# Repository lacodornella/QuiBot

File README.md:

# QuiBot

QuiBot is a robot to experiment basic sequential programming for children. No computer is needed as it can be programmed by using painted wooden blocks, where each color represents a different action. The robot has a backpack that can contain up to 12 blocks that execute as soon as they're consumed.

## Project folders

The project uses the following folders:
 - [3D Design](./3D_design/): 3D assembly process, BOM and printing files
 - [ESP-32 Arduino program](./QuiBot/): C++ Arduino program
 - [Kicad PCB project](./PCB_QuiBot/): Kicad PCB project
 - [Images](./Images/): Used to store some project images

## Development

This robot has been conceived and developed by Aleix Badia and [Pau Lafoz](https://www.github.com/pau-lafoz) from La Codornella under the UPC project "Qui-Bot H2O", led by Marta Tarrés and Toni Dorado, and funded by FECYT.

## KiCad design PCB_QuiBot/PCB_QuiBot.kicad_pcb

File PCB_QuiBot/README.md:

# QuiBot Kicad Project

## 3D View

## Layout

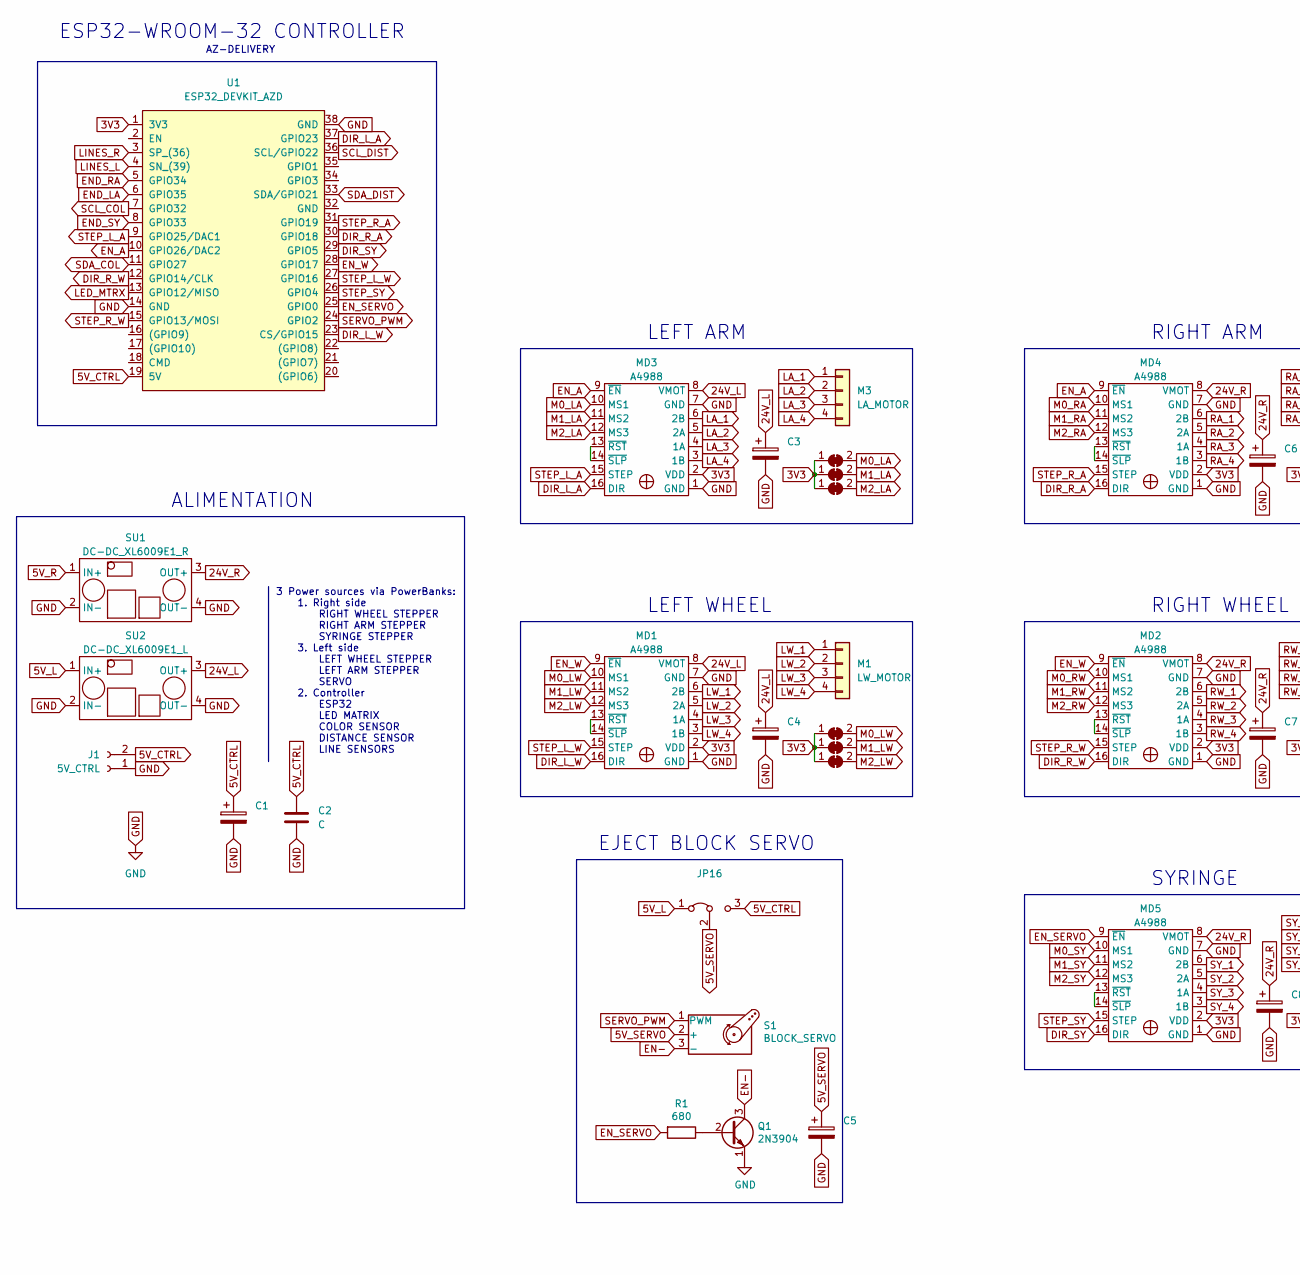
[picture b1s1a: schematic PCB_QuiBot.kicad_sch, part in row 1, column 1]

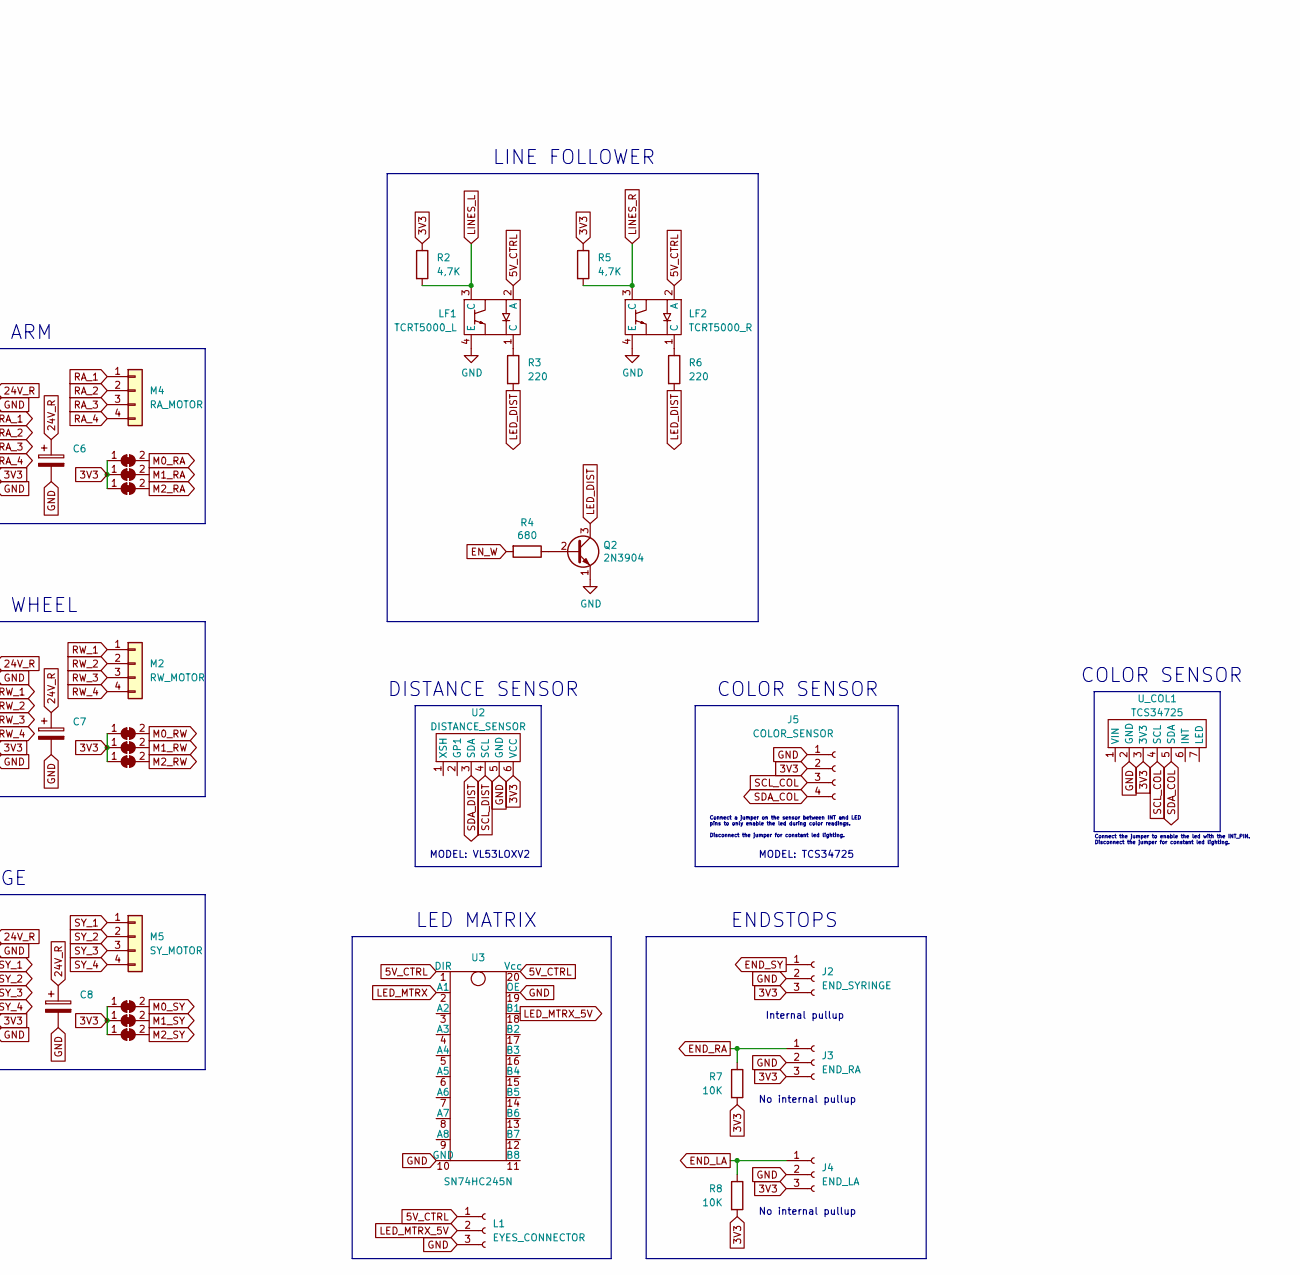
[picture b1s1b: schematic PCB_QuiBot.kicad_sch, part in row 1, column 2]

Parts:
C1: (no value)
C2: C; C_Disc_D4.3mm_W1.9mm_P5.00mm
C3, C4, C5, C6, C7, C8: C_Polarized; CP_Flat_position
J1: 5V_CTRL; PCB_cable_soldering
J2: END_SYRINGE; PinHeader_1x03_P2.54mm_Vertical
J3: END_RA; PinHeader_1x03_P2.54mm_Vertical
J4: END_LA; PinHeader_1x03_P2.54mm_Vertical
J5: COLOR_SENSOR; PinHeader_1x04_P2.54mm_Vertical
JP1, JP2, JP3, JP4, JP5, JP6, JP7, JP8, JP9, JP10, JP11, JP12, JP13, JP14, JP15: SolderJumper_2_Bridged; SolderJumper-2_P1.3mm_Bridged_RoundedPad1.0x1.5mm
JP16: (no value)
L1: EYES_CONNECTOR; PinHeader_1x03_P2.54mm_Vertical
LF1: TCRT5000_L; TCRT5000_Line_follower
LF2: TCRT5000_R; TCRT5000_Line_follower
M1: LW_MOTOR; PinHeader_1x04_P2.54mm_Vertical
M2: RW_MOTOR; PinHeader_1x04_P2.54mm_Vertical
M3: LA_MOTOR; PinHeader_1x04_P2.54mm_Vertical
M4: RA_MOTOR; PinHeader_1x04_P2.54mm_Vertical
M5: SY_MOTOR; PinHeader_1x04_P2.54mm_Vertical
MD1, MD2, MD3, MD4, MD5: A4988; A4988_stepper_driver
Q1, Q2: 2N3904; TO-92_Inline_Wide
R1, R4: 680; R_Axial_DIN0207_L6.3mm_D2.5mm_P10.16mm_Horizontal
R2, R5: 4,7K; R_Axial_DIN0207_L6.3mm_D2.5mm_P10.16mm_Horizontal
R3, R6: 220; R_Axial_DIN0207_L6.3mm_D2.5mm_P10.16mm_Horizontal
R7, R8: 10K; R_Axial_DIN0207_L6.3mm_D2.5mm_P10.16mm_Horizontal
S1: BLOCK_SERVO; PinHeader_1x03_P2.54mm_Vertical
SU1: DC-DC_XL6009E1_R
SU2: DC-DC_XL6009E1_L
U1: ESP32_DEVKIT_AZD; ESP32_DevKit_AZD
U2: DISTANCE_SENSOR; PinHeader_1x06_P2.54mm_Vertical
U3: SN74HC245N
U_COL1: TCS34725

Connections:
3V3: J2.3, J3.3, J4.3, J5.2, JP1.1 (A), JP2.1 (A), JP3.1 (A), JP4.1 (A), JP5.1 (A), JP6.1 (A), JP7.1 (A), JP8.1 (A), JP9.1 (A), JP10.1 (A), JP11.1 (A), JP12.1 (A), JP13.1 (A), JP14.1 (A), JP15.1 (A), MD1.2 (VDD), MD2.2 (VDD), MD3.2 (VDD), MD4.2 (VDD), MD5.2 (VDD), R2.1, R5.1, R7.2, R8.2, U1.1 (3V3), U2.6 (VCC), U_COL1.3 (3V3)
5V_CTRL: C1.1, C2.1, J1.2, JP16.3 (B), L1.1, LF1.2 (A), LF2.2 (A), U1.19 (5V), U3.1 (DIR), U3.20 (Vcc)
5V_L: JP16.1 (A), SU2.1 (IN+)
5V_R: SU1.1 (IN+)
5V_SERVO: C5.1, JP16.2 (C), S1.2 (+)
24V_L: C3.1, C4.1, MD1.8 (VMOT), MD3.8 (VMOT), SU2.3 (OUT+)
24V_R: C6.1, C7.1, C8.1, MD2.8 (VMOT), MD4.8 (VMOT), MD5.8 (VMOT), SU1.3 (OUT+)
DIR_L_A: MD3.16 (DIR), U1.37 (GPIO23)
DIR_L_W: MD1.16 (DIR), U1.23 (CS/GPIO15)
DIR_R_A: MD4.16 (DIR), U1.30 (GPIO18)
DIR_R_W: MD2.16 (DIR), U1.12 (GPIO14/CLK)
DIR_SY: MD5.16 (DIR), U1.29 (GPIO5)
EN-: Q1.3 (C), S1.3 (-)
END_LA: J4.1, R8.1, U1.6 (GPIO35)
END_RA: J3.1, R7.1, U1.5 (GPIO34)
END_SY: J2.1, U1.8 (GPIO33)
EN_A: MD3.9 (~EN), MD4.9 (~EN), U1.10 (GPIO26/DAC2)
EN_SERVO: MD5.9 (~EN), R1.2, U1.25 (GPIO0)
EN_W: MD1.9 (~EN), MD2.9 (~EN), R4.2, U1.28 (GPIO17)
GND: C1.2, C2.2, C3.2, C4.2, C5.2, C6.2, C7.2, C8.2, J1.1, J2.2, J3.2, J4.2, J5.1, L1.3, LF1.4 (E), LF2.4 (E), MD1.1 (GND), MD1.7 (GND), MD2.1 (GND), MD2.7 (GND), MD3.1 (GND), MD3.7 (GND), MD4.1 (GND), MD4.7 (GND), MD5.1 (GND), MD5.7 (GND), Q1.1 (E), Q2.1 (E), SU1.2 (IN-), SU1.4 (OUT-), SU2.2 (IN-), SU2.4 (OUT-), U1.14 (GND), U1.38 (GND), U2.5 (GND), U3.10 (GND), U3.19 (OE), U_COL1.2 (GND)
LA_1: M3.1, MD3.6 (2B)
LA_2: M3.2, MD3.5 (2A)
LA_3: M3.3, MD3.4 (1A)
LA_4: M3.4, MD3.3 (1B)
LED_DIST: Q2.3 (C), R3.2, R6.2
LED_MTRX: U1.13 (GPIO12/MISO), U3.2 (A1)
LED_MTRX_5V: L1.2, U3.18 (B1)
LINES_L: LF1.3 (C), R2.2, U1.4 (SN_(39))
LINES_R: LF2.3 (C), R5.2, U1.3 (SP_(36))
LW_1: M1.1, MD1.6 (2B)
LW_2: M1.2, MD1.5 (2A)
LW_3: M1.3, MD1.4 (1A)
LW_4: M1.4, MD1.3 (1B)
M0_LA: JP1.2 (B), MD3.10 (MS1)
M0_LW: JP4.2 (B), MD1.10 (MS1)
M0_RA: JP7.2 (B), MD4.10 (MS1)
M0_RW: JP10.2 (B), MD2.10 (MS1)
M0_SY: JP13.2 (B), MD5.10 (MS1)
M1_LA: JP2.2 (B), MD3.11 (MS2)
M1_LW: JP5.2 (B), MD1.11 (MS2)
M1_RA: JP8.2 (B), MD4.11 (MS2)
M1_RW: JP11.2 (B), MD2.11 (MS2)
M1_SY: JP14.2 (B), MD5.11 (MS2)
M2_LA: JP3.2 (B), MD3.12 (MS3)
M2_LW: JP6.2 (B), MD1.12 (MS3)
M2_RA: JP9.2 (B), MD4.12 (MS3)
M2_RW: JP12.2 (B), MD2.12 (MS3)
M2_SY: JP15.2 (B), MD5.12 (MS3)
unnamed: LF1.1 (C), R3.1
unnamed: LF2.1 (C), R6.1
unnamed: MD1.13 (~RST), MD1.14 (~SLP)
unnamed: MD2.13 (~RST), MD2.14 (~SLP)
unnamed: MD3.13 (~RST), MD3.14 (~SLP)
unnamed: MD4.13 (~RST), MD4.14 (~SLP)
unnamed: MD5.13 (~RST), MD5.14 (~SLP)
unnamed: Q1.2 (B), R1.1
unnamed: Q2.2 (B), R4.1
RA_1: M4.1, MD4.6 (2B)
RA_2: M4.2, MD4.5 (2A)
RA_3: M4.3, MD4.4 (1A)
RA_4: M4.4, MD4.3 (1B)
RW_1: M2.1, MD2.6 (2B)
RW_2: M2.2, MD2.5 (2A)
RW_3: M2.3, MD2.4 (1A)
RW_4: M2.4, MD2.3 (1B)
SCL_COL: J5.3, U1.7 (GPIO32), U_COL1.4 (SCL)
SCL_DIST: U1.36 (SCL/GPIO22), U2.4 (SCL)
SDA_COL: J5.4, U1.11 (GPIO27), U_COL1.5 (SDA)
SDA_DIST: U1.33 (SDA/GPIO21), U2.3 (SDA)
SERVO_PWM: S1.1 (PWM), U1.24 (GPIO2)
STEP_L_A: MD3.15 (STEP), U1.9 (GPIO25/DAC1)
STEP_L_W: MD1.15 (STEP), U1.27 (GPIO16)
STEP_R_A: MD4.15 (STEP), U1.31 (GPIO19)
STEP_R_W: MD2.15 (STEP), U1.15 (GPIO13/MOSI)
STEP_SY: MD5.15 (STEP), U1.26 (GPIO4)
SY_1: M5.1, MD5.6 (2B)
SY_2: M5.2, MD5.5 (2A)
SY_3: M5.3, MD5.4 (1A)
SY_4: M5.4, MD5.3 (1B)

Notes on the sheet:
No internal pullup
ALIMENTATION
MODEL: VL53LOXV2
RIGHT WHEEL
MODEL: TCS34725
COLOR SENSOR
EJECT BLOCK SERVO
ENDSTOPS
LEFT ARM
ESP32-WROOM-32 CONTROLLER
AZ-DELIVERY
SYRINGE
LINE FOLLOWER
Connect a jumper on the sensor between INT and LED pins to only enable the led during color readings. Disconnect the jumper for constant led lighting.
LEFT WHEEL
DISTANCE SENSOR
LED MATRIX
3 Power sources via PowerBanks: 1. Right side RIGHT WHEEL STEPPER RIGHT ARM STEPPER SYRINGE STEPPER 3. Left side LEFT WHEEL STEPPER LEFT ARM STEPPER SERVO 2. Controller ESP32 LED MATRIX COLOR SENSOR DISTANCE SENSOR LINE SENSORS
Internal pullup
Connect the jumper to enable the led with the INT_PIN. Disconnect the jumper for constant led lighting.
RIGHT ARM

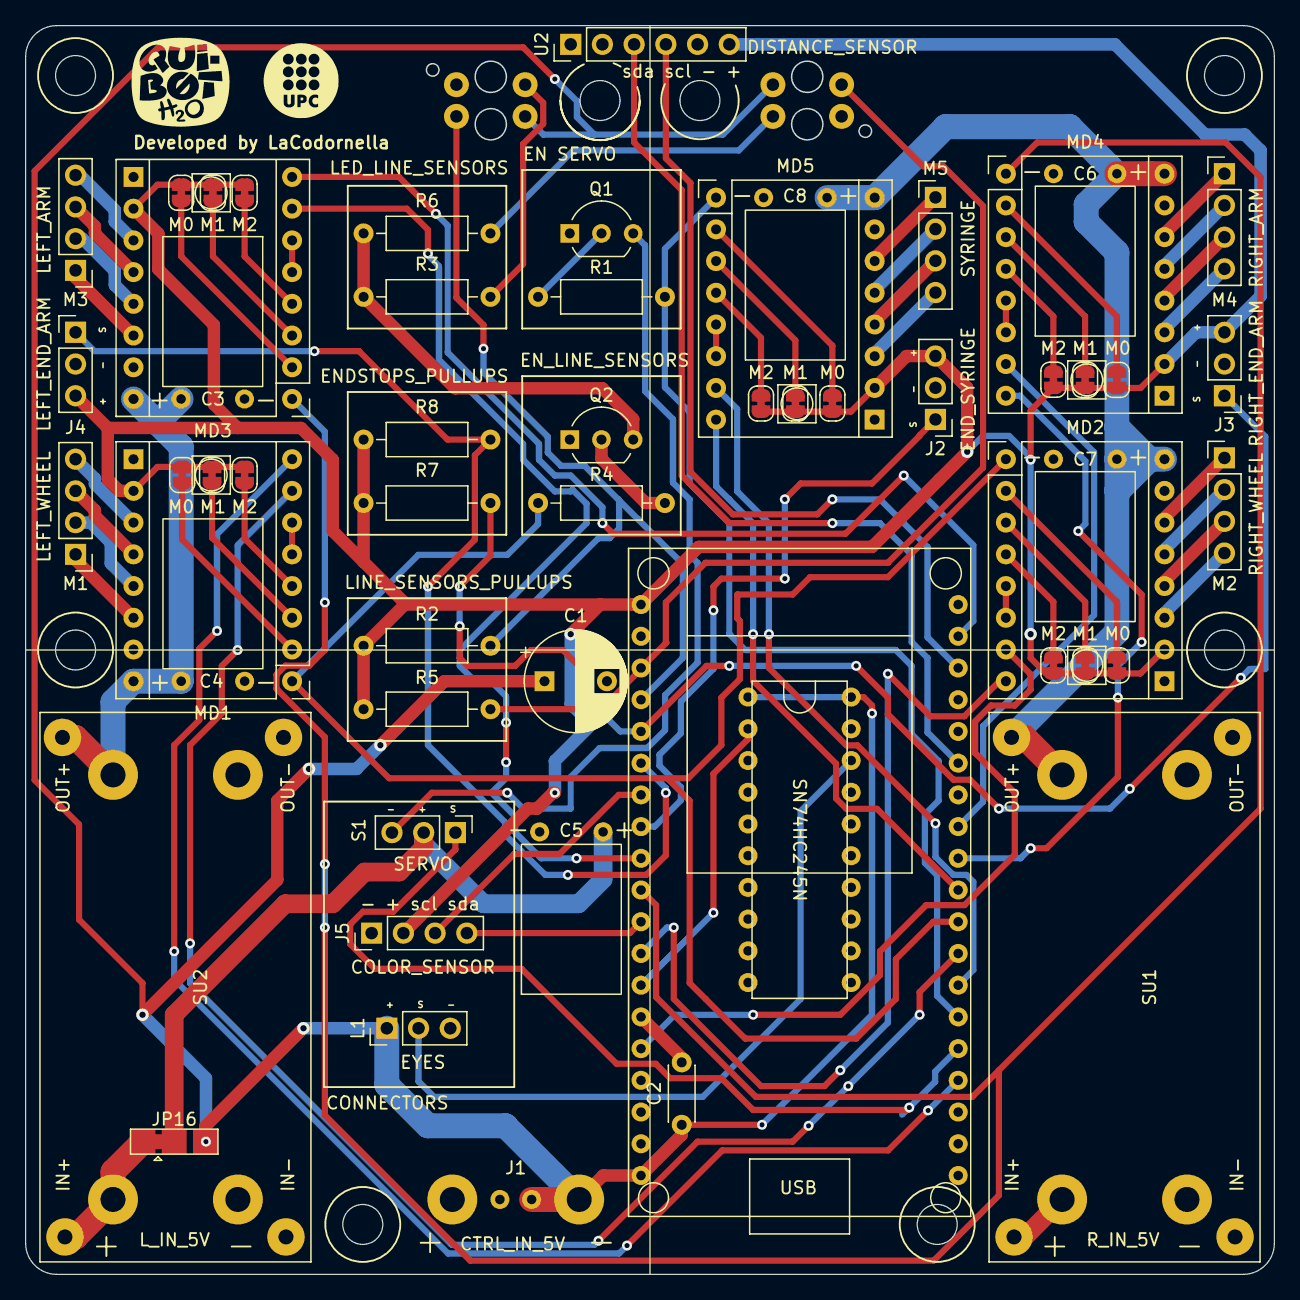
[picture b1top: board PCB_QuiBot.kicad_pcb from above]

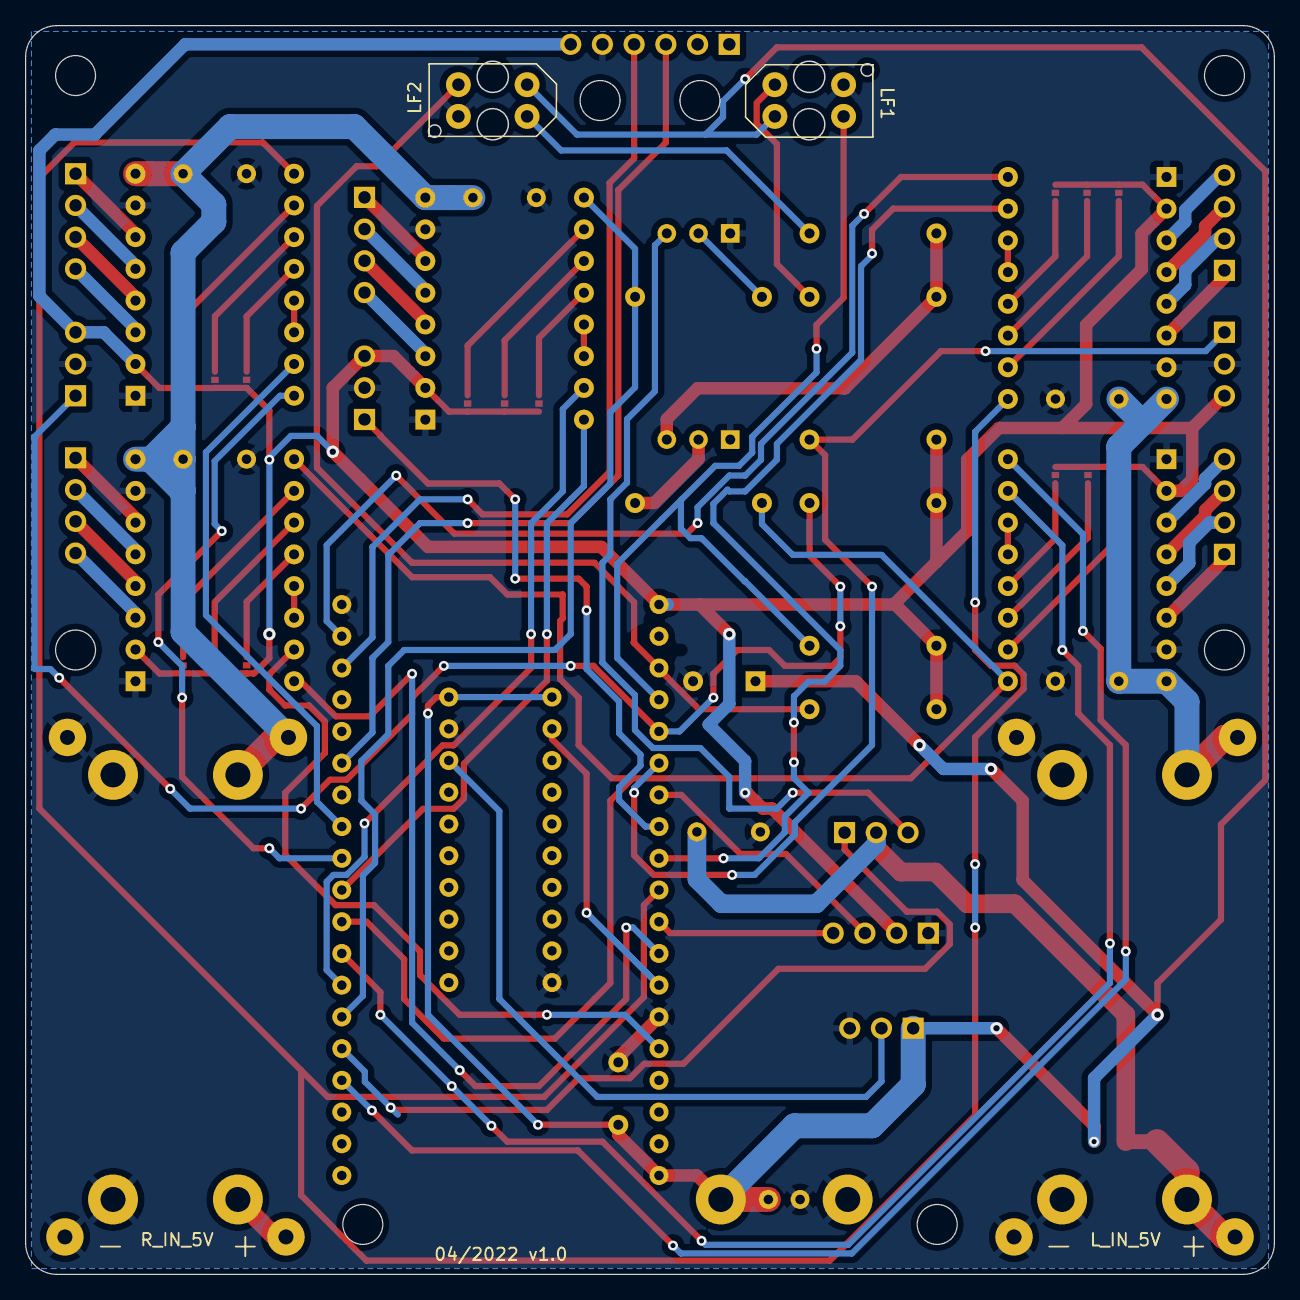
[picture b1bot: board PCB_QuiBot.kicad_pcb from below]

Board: 2 copper layers, 100.0 x 100.0 mm, 58 parts (2 on the bottom side), 78 nets.

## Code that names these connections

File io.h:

#ifndef IO
#define IO

// Expulse blocks Servo pins
#define EN_SERVO      0
#define SERVO_PWM     2

// Syringe Stepper pins
#define STEP_SYRINGE  4
#define DIR_SYRINGE   5

// Led Matrix Data pin
#define LED_MTRX      12

// Right Wheel Stepper pins
#define STEP_R_W      13
#define DIR_R_W       14

// Left Wheel Stepper pins
#define DIR_L_W       15
#define STEP_L_W      16

// Wheel Steppers Enable pin
#define EN_W          17

// Right Arm Stepper pins
#define DIR_R_A       18
#define STEP_R_A      19

// Left Arm Stepper pins
#define DIR_L_A       23
#define STEP_L_A      25

// Arm Steppers Enable pin
#define EN_A          26

// I2C Distance sensor pins
#define SDA_DIST      21
#define SCL_DIST      22

// I2C Color sensor pins
#define SDA_COL       27
#define SCL_COL       32

// Syringe Endstop 
#define END_SYRINGE   33

// Right Arm Endstop
#define END_R_A       34

// Left Arm Endstop
#define END_L_A       35

// Line Follower Sensors
#define LINES_R       36
#define LINES_L       39

#endif

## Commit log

2022-05-23 First working QuiBot prototype
2022-05-23 Readme created
2022-05-23 Added libraries
2022-05-23 Development created
2022-05-23 Some comments added
2022-05-23 Deleted some commented lines
2022-05-23 Photo added to readme
2022-05-23 Changed photo call
2022-05-24 Added Kicad project
2022-05-24 Added PCB images, pdf schematic and readme
2022-05-30 Docs added
2022-05-30 Assembly process added
2022-05-30 Readme updated
2022-05-30 BOM added
2022-05-30 BOM on readme
2022-05-30 3D parts list added
2022-05-30 Printing considerations
2022-05-30 Arduino program readme
2022-05-30 Links on folders
2022-05-30 Added pau's github link
2022-05-30 Account link modified
2022-05-30 QuiBot playing area
2022-05-31 User manual added
2022-06-02 PDF added to improve readability
2022-06-02 PDF links added
2022-06-02 FDM printer
2022-06-02 Link repaired
2022-06-02 Reduced images
2022-06-14 Motion changes. Wheels always in speed mode.
2022-06-16 Eyes down. Waits if object is in front.
